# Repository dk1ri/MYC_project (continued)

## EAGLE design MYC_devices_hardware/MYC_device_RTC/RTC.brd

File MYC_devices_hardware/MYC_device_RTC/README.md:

#Real Time Clock
This is a device, which can deliver 
accurate time data to a MYC system

The DCF RTC board by ELV is used, which receives the DCF77 signal from Franfurt.

For details of the MYC protocol see the documentation or read www.dk1ri.de -> MYC

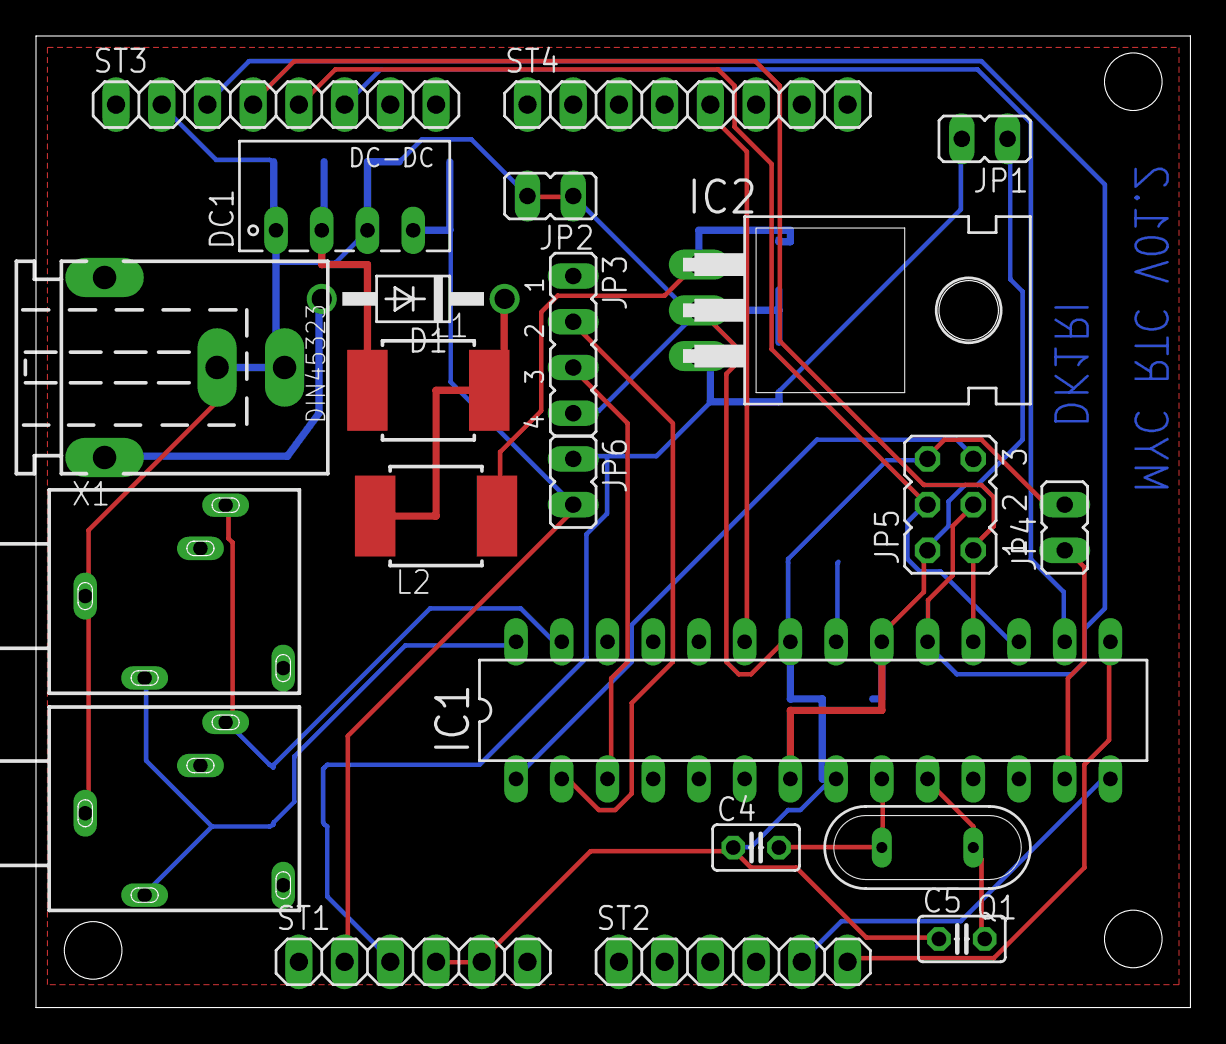
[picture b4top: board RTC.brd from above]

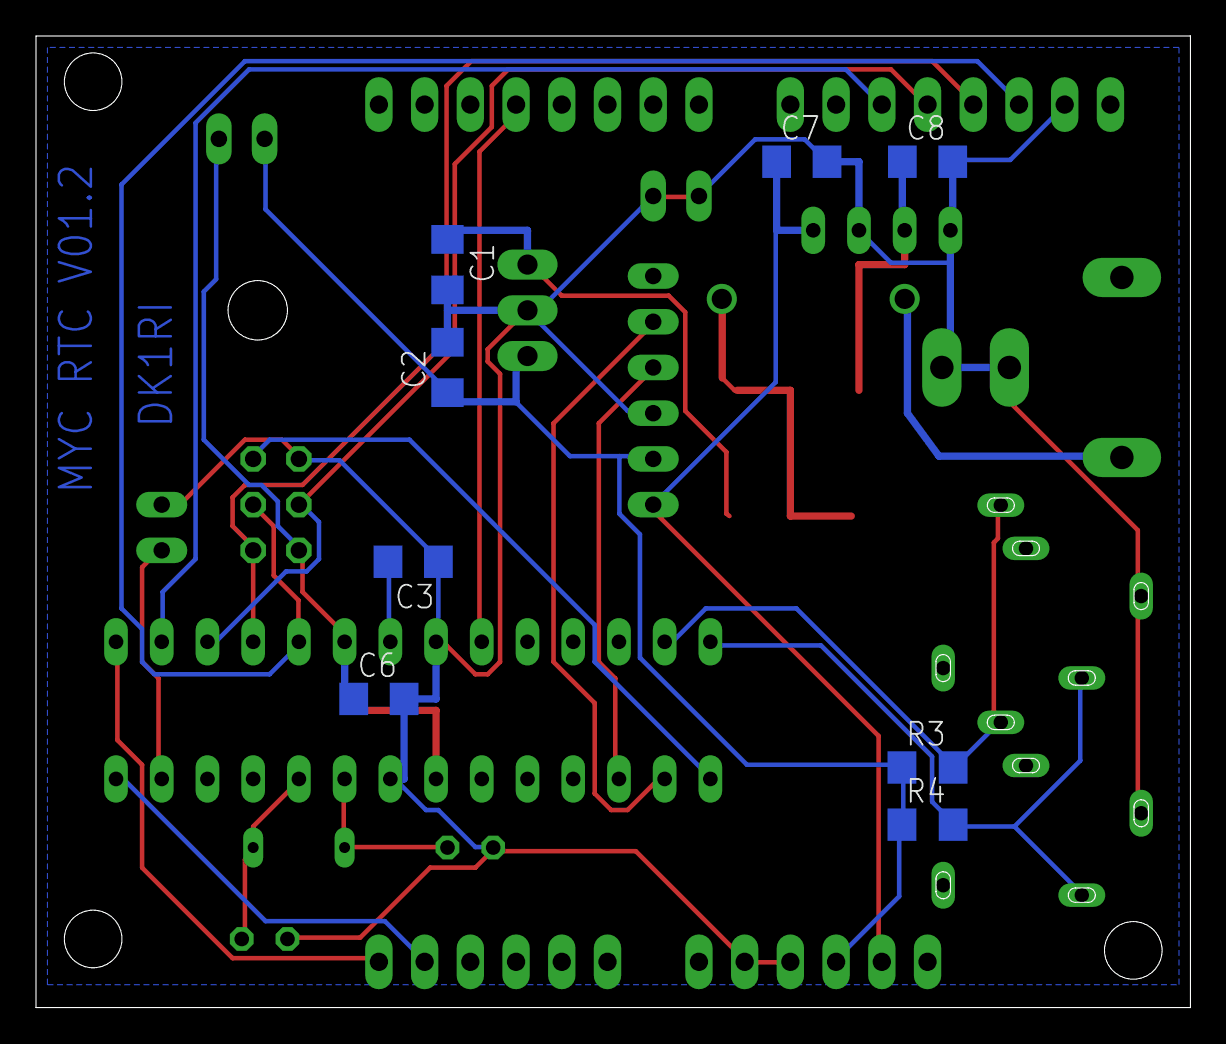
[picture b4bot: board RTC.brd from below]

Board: 2 copper layers, 64.1 x 54.0 mm, 30 parts (8 on the bottom side), 24 nets.

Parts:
C1, C2, C3, C6, C7, C8: 22uF 1210; C1206
C4, C5: 18pF; C025-025X050
D1: 1N4004; DO41-10
DC1: AM1S1203SZ; NME
IC1: MEGA8-P; DIL28-3
IC2: 7805T; TO220H
JP1: Power; JP1
JP2: GND; JP1
JP3: USB; JP4
JP4: Reset; JP1
JP5: ISP; JP3Q
JP6: USB2; JP1
L1, L2: 100u; MS85
Q1: 20MHz; QS
R3, R4: 4k7; R1206
ST1: Power; 1X06
ST2: I2C; 1X06
ST3: SPI; 1X08
ST4: UART; 1X08
X1: 8-15V; 737992-5
X2, X3: 1503_09

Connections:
GND: C1.2, C2.2, C3.1, C4.1, C5.1, C6.2, C7.2, C8.2, DC1.1, DC1.3, IC1.8, IC1.22, IC2.2, JP2.1, JP2.2, JP3.4, JP4.2, JP5.6, ST1.4, ST1.5, ST3.2, X1.+, X1.K, X2.1, X3.1
unnamed: IC1.23, ST4.5
unnamed: IC1.14, ST2.5
unnamed: C8.1, DC1.2, L1.2
unnamed: IC1.16, ST3.6
unnamed: IC1.27, R3.2, X2.3, X3.3
unnamed: IC1.13, JP4.1
unnamed: D1.C, L1.1, L2.1
unnamed: IC1.3, JP3.3
unnamed: IC1.2, JP3.2
unnamed: IC1.15, ST2.6
unnamed: IC1.18, JP5.1, ST3.4
unnamed: IC1.1, JP5.5
unnamed: C4.2, IC1.9, Q1.2
unnamed: IC1.19, JP5.3, ST3.3
unnamed: IC1.28, R4.2, X2.2, X3.2
unnamed: D1.A, X1.-1
unnamed: IC1.17, JP5.4, ST3.5
unnamed: C1.1, IC2.1, L2.2
unnamed: C3.2, IC1.21
unnamed: C5.2, IC1.10, Q1.1
unnamed: C6.1, IC1.7, IC1.20, JP1.1, JP5.2
VDD: C2.1, IC2.3, JP1.2, JP6.1, R3.1, R4.1, ST1.3
VSS: C7.1, DC1.4, JP6.2, ST1.2

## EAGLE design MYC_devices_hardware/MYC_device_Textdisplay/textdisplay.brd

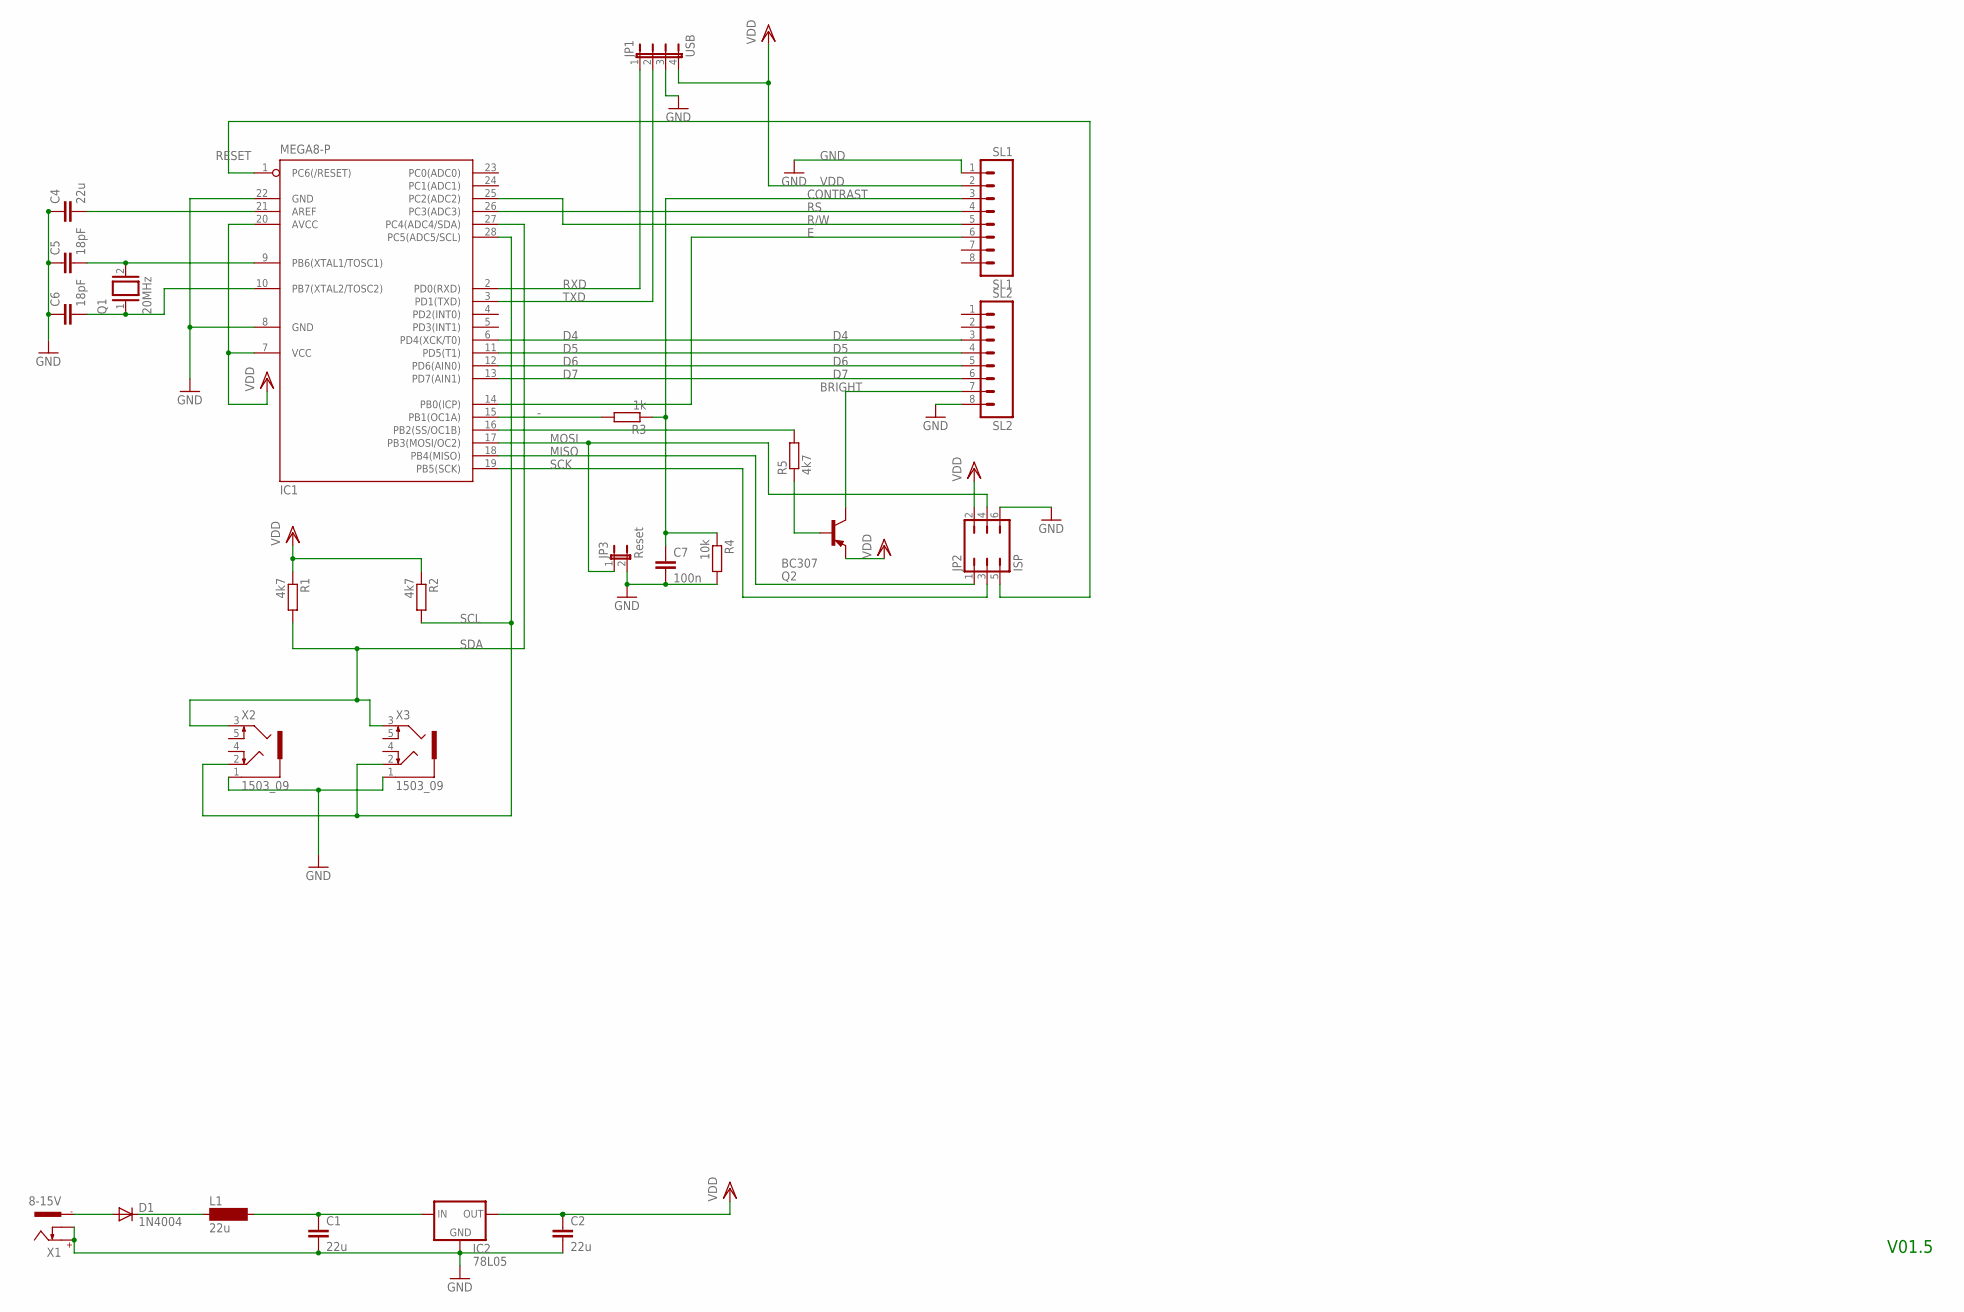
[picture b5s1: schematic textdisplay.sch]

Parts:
C1, C2, C4: 22u; C1206
C5, C6: 18pF; C025-025X050
C7: 100n; C050-025X075
D1: 1N4004; DO41-10
IC1: MEGA8-P; DIL28-3
IC2: 78L05; 78LXX
JP1: USB; JP4
JP2: ISP; JP3Q
JP3: Reset; JP1
L1: 22u; MS85
Q1: 20MHz; QS
Q2: BC307; TO92
R1, R2, R5: 4k7; 0207/2V
R3: 1k; 0207/2V
R4: 10k; 0207/2V
SL1: SL1; 08P
SL2: SL2; 08P
X1: 8-15V; 737992-5
X2, X3: 1503_09

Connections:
-: IC1.15 (PB1(OC1A)), R3.2
BRIGHT: Q2.3 (C), SL2.7
CONTRAST: C7.1, R3.1, R4.1, SL1.3
D4: IC1.6 (PD4(XCK/T0)), SL2.3
D5: IC1.11 (PD5(T1)), SL2.4
D6: IC1.12 (PD6(AIN0)), SL2.5
D7: IC1.13 (PD7(AIN1)), SL2.6
E: IC1.14 (PB0(ICP)), SL1.6
GND: C1.2, C2.2, C4.1, C5.1, C6.1, C7.2, IC1.8 (GND), IC1.22 (GND), IC2.GND, JP1.3, JP2.6, JP3.2, R4.2, SL1.1, SL2.8, X1.+, X1.K, X2.1, X3.1
MISO: IC1.18 (PB4(MISO)), JP2.1
MOSI: IC1.17 (PB3(MOSI/OC2)), JP2.4, JP3.1
unnamed: D1.C, L1.1
unnamed: IC1.16 (PB2(SS/OC1B)), R5.2
unnamed: Q2.2 (B), R5.1
unnamed: C1.1, IC2.IN, L1.2
unnamed: C5.2, IC1.9 (PB6(XTAL1/TOSC1)), Q1.2
unnamed: D1.A, X1.-1
unnamed: C4.2, IC1.21 (AREF)
unnamed: C6.2, IC1.10 (PB7(XTAL2/TOSC2)), Q1.1
R/W: IC1.25 (PC2(ADC2)), SL1.5
RESET: IC1.1 (PC6(/RESET)), JP2.5
RS: IC1.26 (PC3(ADC3)), SL1.4
RXD: IC1.2 (PD0(RXD)), JP1.1
SCK: IC1.19 (PB5(SCK)), JP2.3
SCL: IC1.28 (PC5(ADC5/SCL)), R2.2, X2.2, X3.2
SDA: IC1.27 (PC4(ADC4/SDA)), R1.2, X2.3, X3.3
TXD: IC1.3 (PD1(TXD)), JP1.2
VDD: C2.1, IC1.7 (VCC), IC1.20 (AVCC), IC2.OUT, JP1.4, JP2.2, Q2.1 (E), R1.1, R2.1, SL1.2

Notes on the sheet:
V01.5

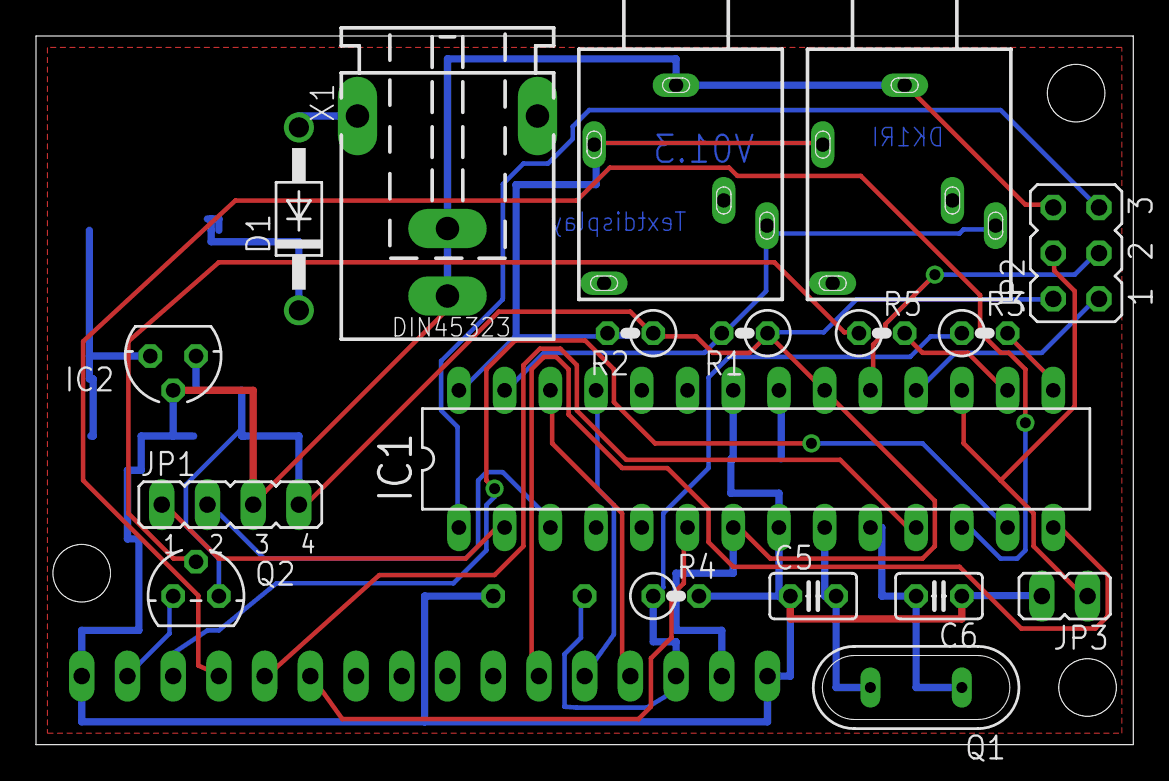
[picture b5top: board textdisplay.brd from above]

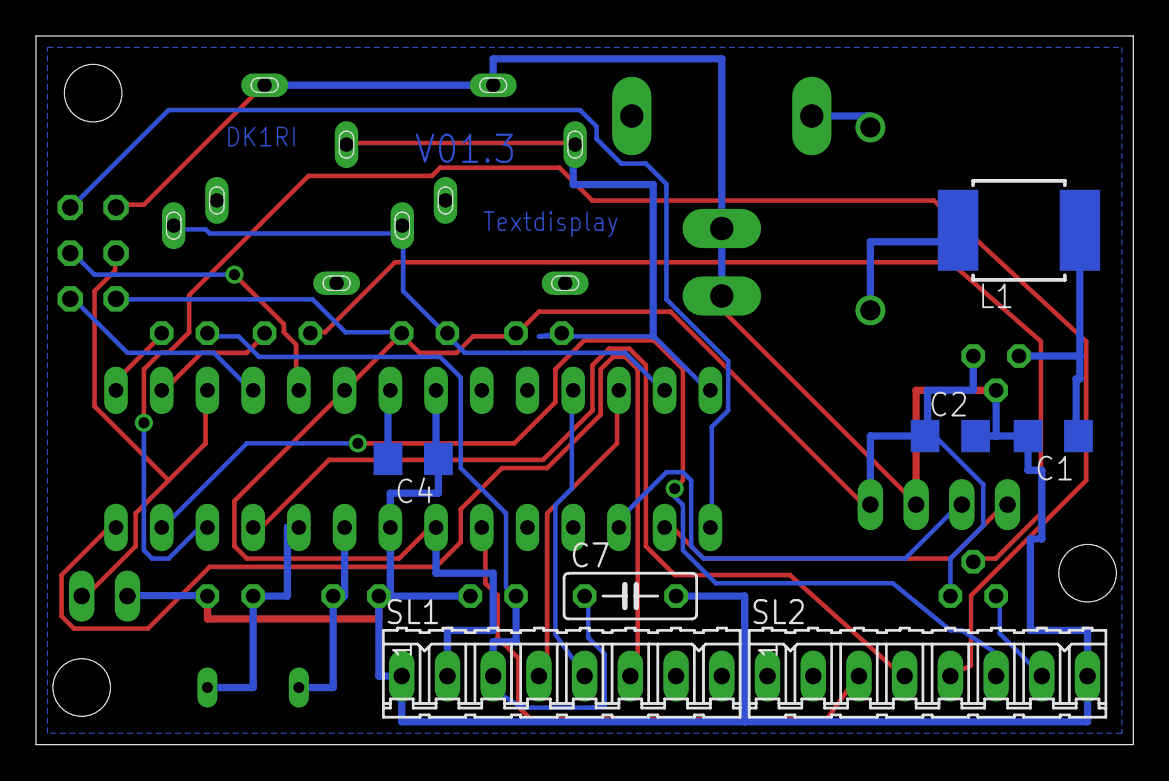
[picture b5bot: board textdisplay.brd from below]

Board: 2 copper layers, 61.0 x 39.4 mm, 25 parts (7 on the bottom side), 28 nets.

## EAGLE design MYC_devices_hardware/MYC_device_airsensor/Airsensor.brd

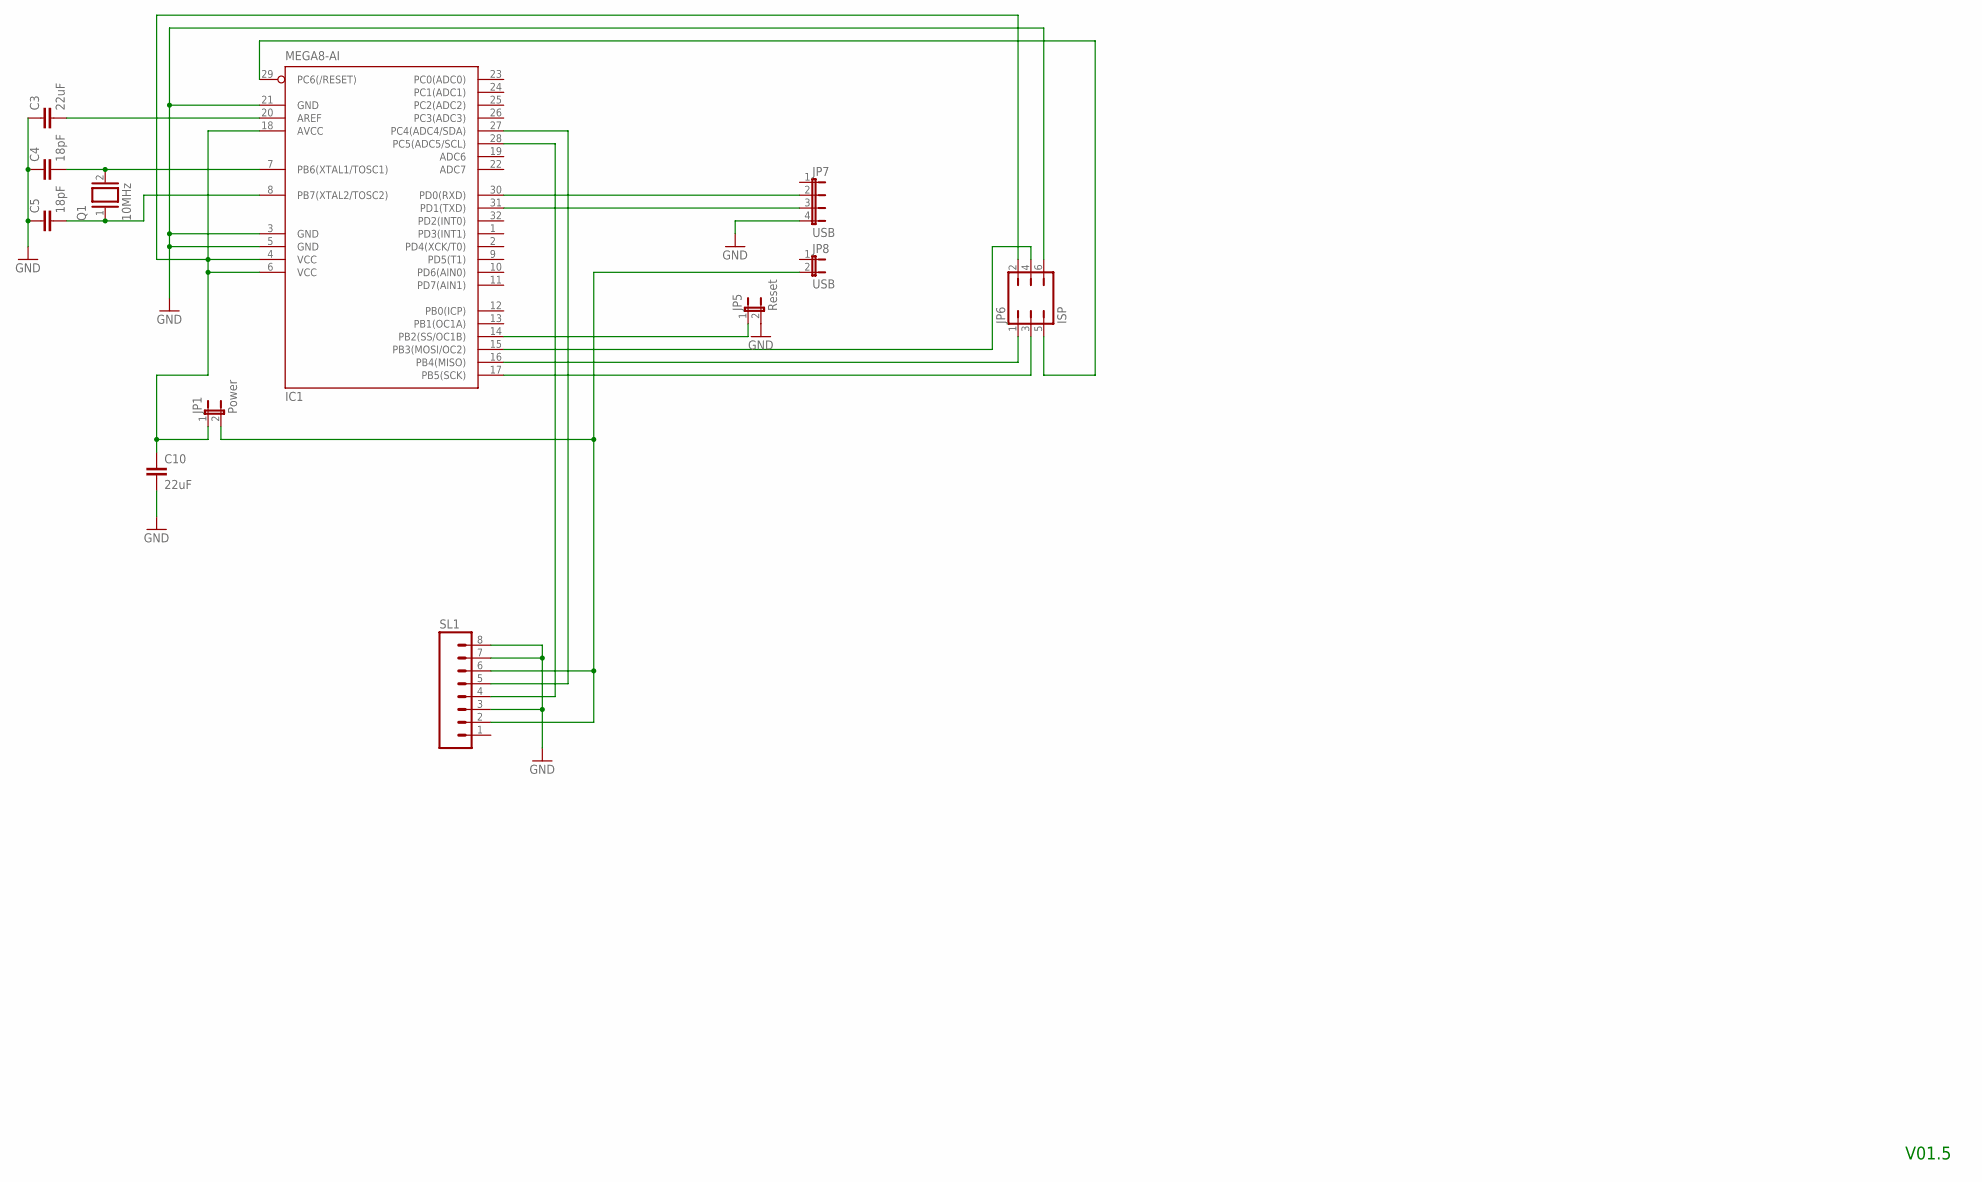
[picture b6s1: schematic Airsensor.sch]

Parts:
C3, C10: 22uF; C1206
C4, C5: 18pF; C025-025X050
IC1: MEGA8-AI; TQFP32-08
JP1: Power; JP1
JP5: Reset; JP1
JP6: ISP; JP3Q
JP7: USB; JP4
JP8: USB; JP1
Q1: 10MHz; QS
SL1: M08; 08P

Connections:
GND: C3.1, C4.1, C5.1, C10.2, IC1.3 (GND), IC1.5 (GND), IC1.21 (GND), JP5.2, JP6.6, JP7.4, SL1.3, SL1.7, SL1.8
unnamed: IC1.28 (PC5(ADC5/SCL)), SL1.4
unnamed: IC1.15 (PB3(MOSI/OC2)), JP6.4
unnamed: JP1.2, JP8.2, SL1.2, SL1.6
unnamed: IC1.17 (PB5(SCK)), JP6.3
unnamed: IC1.31 (PD1(TXD)), JP7.3
unnamed: IC1.14 (PB2(SS/OC1B)), JP5.1
unnamed: IC1.27 (PC4(ADC4/SDA)), SL1.5
unnamed: C3.2, IC1.20 (AREF)
unnamed: IC1.16 (PB4(MISO)), JP6.1
unnamed: IC1.29 (PC6(/RESET)), JP6.5
unnamed: C4.2, IC1.7 (PB6(XTAL1/TOSC1)), Q1.2
unnamed: C10.1, IC1.4 (VCC), IC1.6 (VCC), IC1.18 (AVCC), JP1.1, JP6.2
unnamed: IC1.30 (PD0(RXD)), JP7.2
unnamed: C5.2, IC1.8 (PB7(XTAL2/TOSC2)), Q1.1

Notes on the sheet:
V01.5

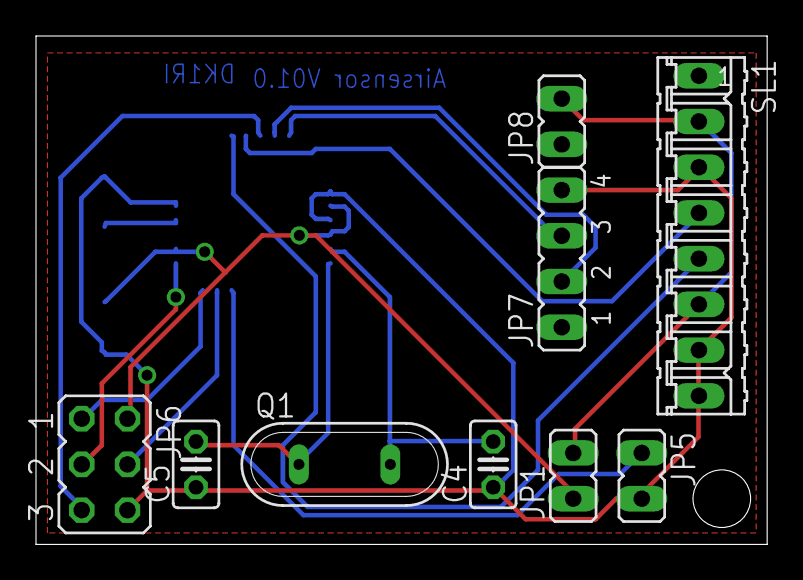
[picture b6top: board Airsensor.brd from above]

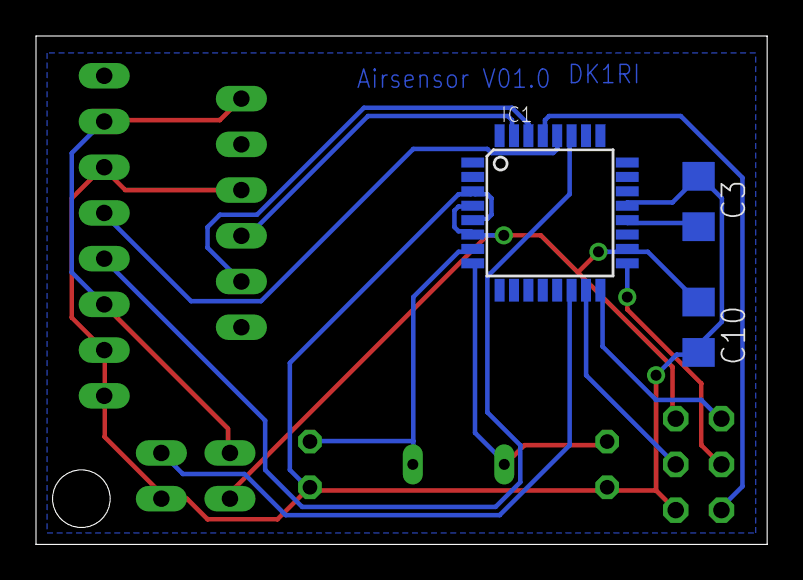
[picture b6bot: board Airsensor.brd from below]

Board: 2 copper layers, 40.6 x 28.2 mm, 12 parts (3 on the bottom side), 15 nets.

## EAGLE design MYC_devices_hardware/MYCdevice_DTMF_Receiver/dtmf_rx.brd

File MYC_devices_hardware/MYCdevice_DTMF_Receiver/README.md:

#DTMF Receiver
This is a MYC device, which can read DTMF Codes

The board can be also used standalone.

For details of the MYC protocol see the documentation or read www.dk1ri.de -> MYC

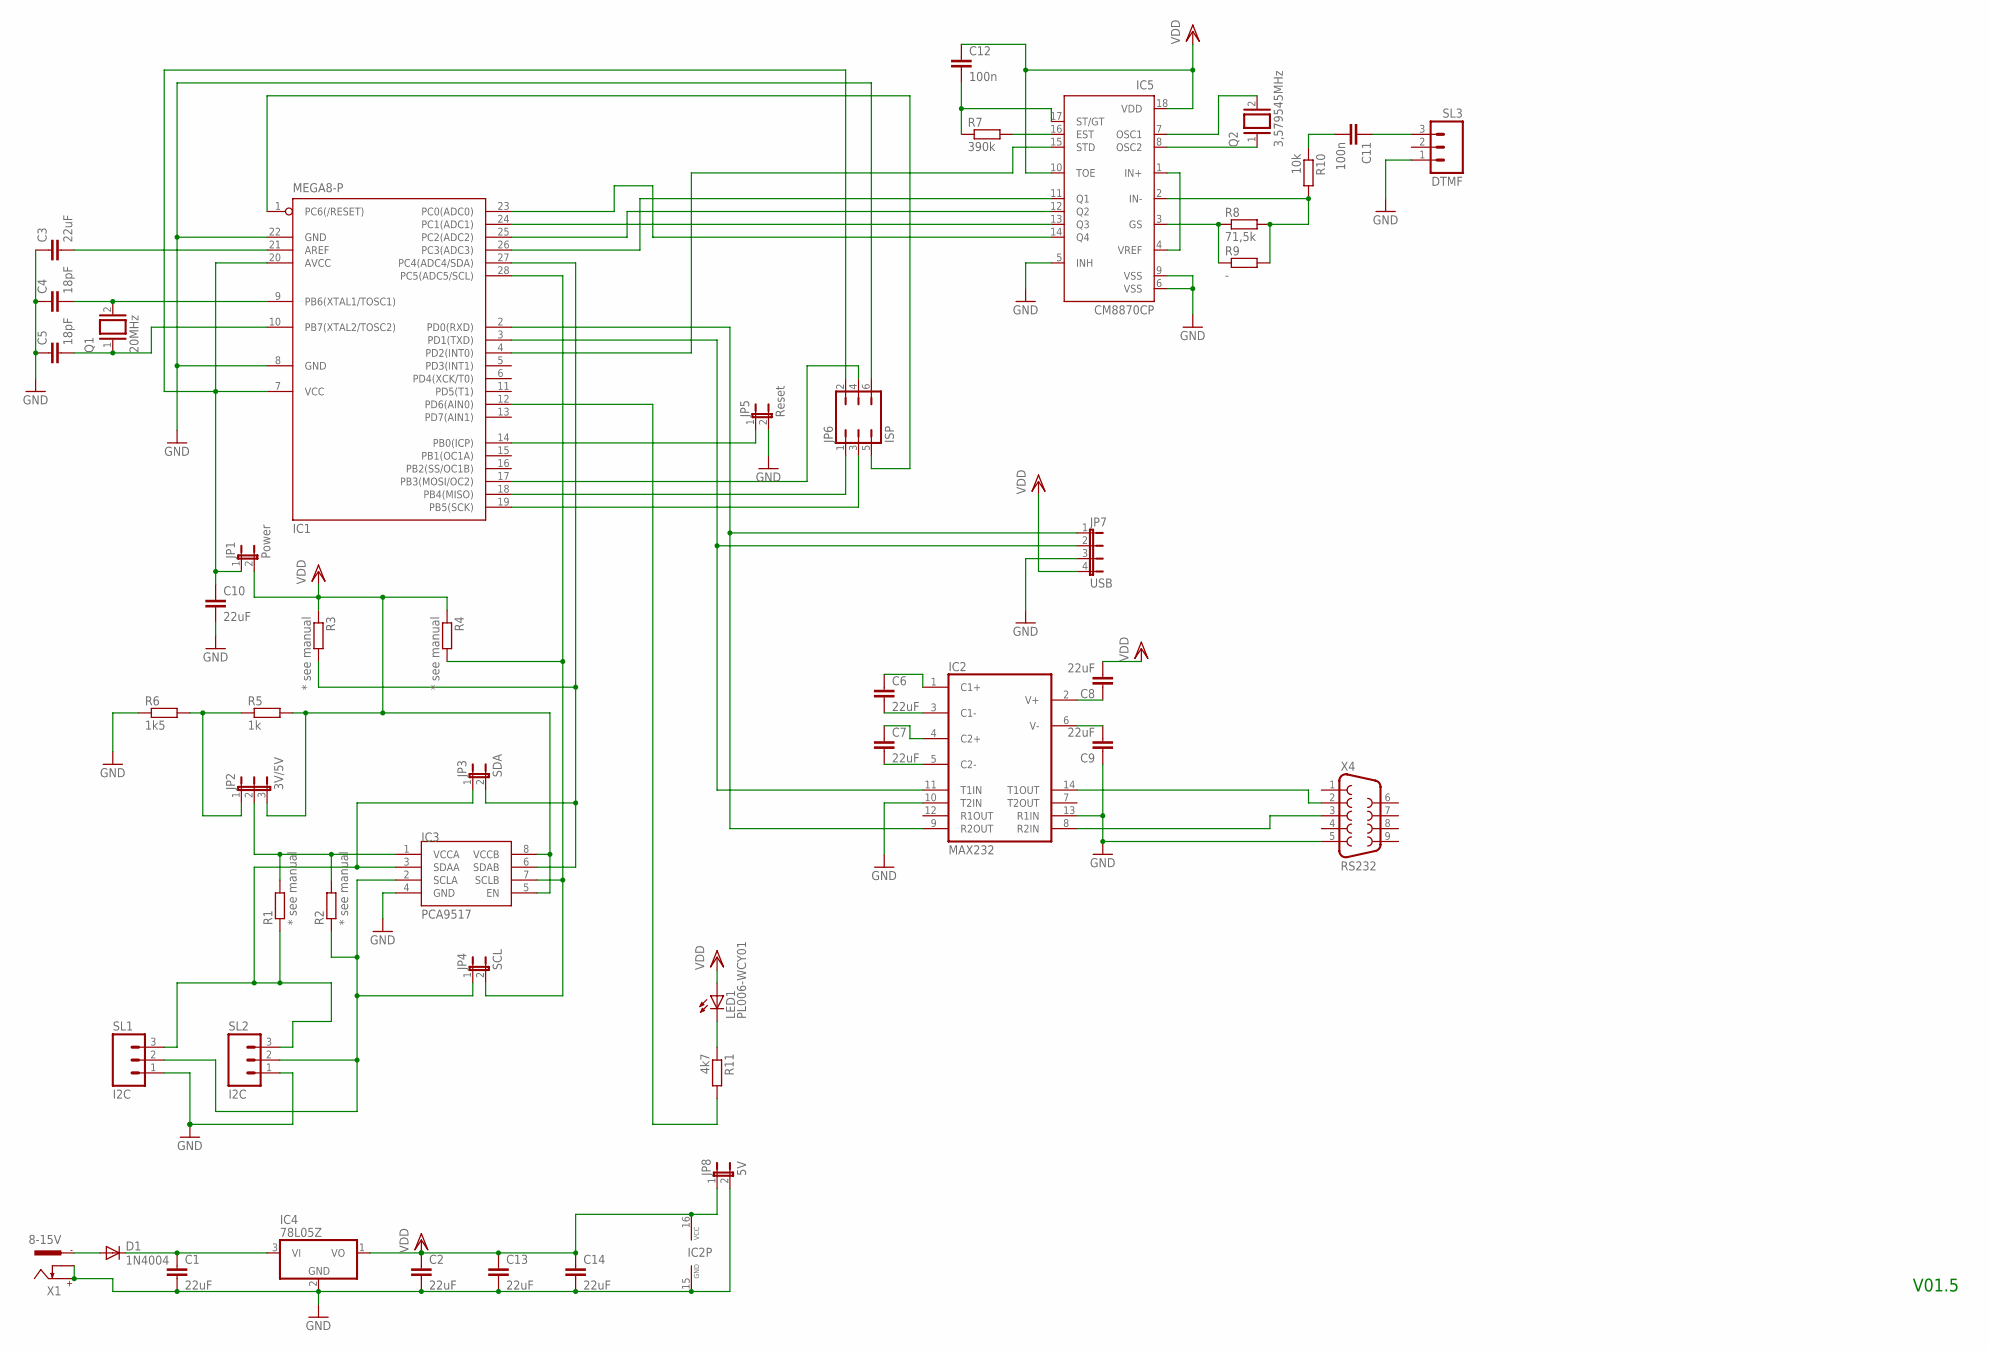
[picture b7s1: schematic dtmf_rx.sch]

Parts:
C1, C2, C3, C6, C7, C8, C9, C10, C13, C14: 22uF; C1206
C4, C5: 18pF; C025-025X050
C11, C12: 100n; C050-025X075
D1: 1N4004; DO41-10
IC1: MEGA8-P; DIL28-3
IC2: MAX232; DIL16
IC3: PCA9517; SO-08
IC4: 78L05Z; TO92
IC5: CM8870CP; DIL18
JP1: Power; JP1
JP2: 3V/5V; JP2
JP3: SDA; JP1
JP4: SCL; JP1
JP5: Reset; JP1
JP6: ISP; JP3Q
JP7: USB; JP4
JP8: 5V; JP1
LED1: PL006-WCY01; SOT23
Q1: 20MHz; QS
Q2: 3,579545MHz; QS
R1, R2, R3, R4: * see manual; R1206
R5: 1k; R1206
R6: 1k5; R1206
R7: 390k; R1206
R8: 71,5k; R1206
R9: -; R1206
R10: 10k; R1206
R11: 4k7; R1206
SL1, SL2: I2C; 03P
SL3: DTMF; 03P
X1: 8-15V; 737992-5
X4: RS232; F09H

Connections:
C13: C6.1, IC2.1 (C1+)
GND: C1.2, C2.2, C3.1, C4.1, C5.1, C9.1, C10.2, C13.2, C14.2, IC1.8 (GND), IC1.22 (GND), IC2.10 (T2IN), IC2.13 (R1IN), IC2.15 (GND), IC3.4 (GND), IC4.2 (GND), IC5.5 (INH), IC5.6 (VSS), IC5.9 (VSS), JP5.2, JP6.6, JP7.3, JP8.2, R6.1, SL1.1, SL2.1, SL3.1, X1.+, X1.K, X4.5
unnamed: IC1.12 (PD6(AIN0)), R11.2
unnamed: IC1.2 (PD0(RXD)), IC2.9 (R2OUT), JP7.1
unnamed: C7.2, IC2.5 (C2-)
unnamed: IC2.14 (T1OUT), X4.2
unnamed: IC3.3 (SDAA), JP3.1, R1.1, SL1.3, SL2.3
unnamed: IC1.14 (PB0(ICP)), JP5.1
unnamed: IC5.1 (IN+), IC5.4 (VREF)
unnamed: IC1.23 (PC0(ADC0)), IC5.14 (Q4)
unnamed: JP2.1, R5.1, R6.2
unnamed: IC2.8 (R2IN), X4.3
unnamed: IC1.3 (PD1(TXD)), IC2.11 (T1IN), JP7.2
unnamed: C7.1, IC2.4 (C2+)
unnamed: C6.2, IC2.3 (C1-)
unnamed: IC1.18 (PB4(MISO)), JP6.1
unnamed: C8.1, IC2.2 (V+)
unnamed: C9.2, IC2.6 (V-)
unnamed: IC1.1 (PC6(/RESET)), JP6.5
unnamed: C4.2, IC1.9 (PB6(XTAL1/TOSC1)), Q1.2
unnamed: IC1.19 (PB5(SCK)), JP6.3
unnamed: C11.1, SL3.3
unnamed: IC1.28 (PC5(ADC5/SCL)), IC3.7 (SCLB), JP4.2, R4.2
unnamed: C11.2, R10.1
unnamed: IC5.2 (IN-), R8.2, R9.2, R10.2
unnamed: IC5.3 (GS), R8.1, R9.1
unnamed: D1.A, X1.-1
unnamed: IC1.17 (PB3(MOSI/OC2)), JP6.4
unnamed: IC5.8 (OSC2), Q2.1
unnamed: IC1.24 (PC1(ADC1)), IC5.13 (Q3)
unnamed: IC5.7 (OSC1), Q2.2
unnamed: IC5.16 (EST), R7.2
unnamed: C1.1, D1.C, IC4.3 (VI)
unnamed: IC1.26 (PC3(ADC3)), IC5.11 (Q1)
unnamed: C3.2, IC1.21 (AREF)
unnamed: IC1.27 (PC4(ADC4/SDA)), IC3.6 (SDAB), JP3.2, R3.2
unnamed: C5.2, IC1.10 (PB7(XTAL2/TOSC2)), Q1.1
unnamed: IC1.25 (PC2(ADC2)), IC5.12 (Q2)
unnamed: IC3.2 (SCLA), JP4.1, R2.1, SL1.2, SL2.2
unnamed: C12.2, IC5.17 (ST/GT), R7.1
unnamed: IC1.4 (PD2(INT0)), IC5.15 (STD)
unnamed: IC3.1 (VCCA), JP2.2, R1.2, R2.2
unnamed: C10.1, IC1.7 (VCC), IC1.20 (AVCC), JP1.1, JP6.2
unnamed: LED1.3 (C), R11.1
VDD: C2.1, C8.2, C12.1, C13.1, C14.1, IC2.16 (VCC), IC3.5 (EN), IC3.8 (VCCB), IC4.1 (VO), IC5.10 (TOE), IC5.18 (VDD), JP1.2, JP2.3, JP7.4, JP8.1, LED1.1 (A), R3.1, R4.1, R5.2

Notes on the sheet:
V01.5

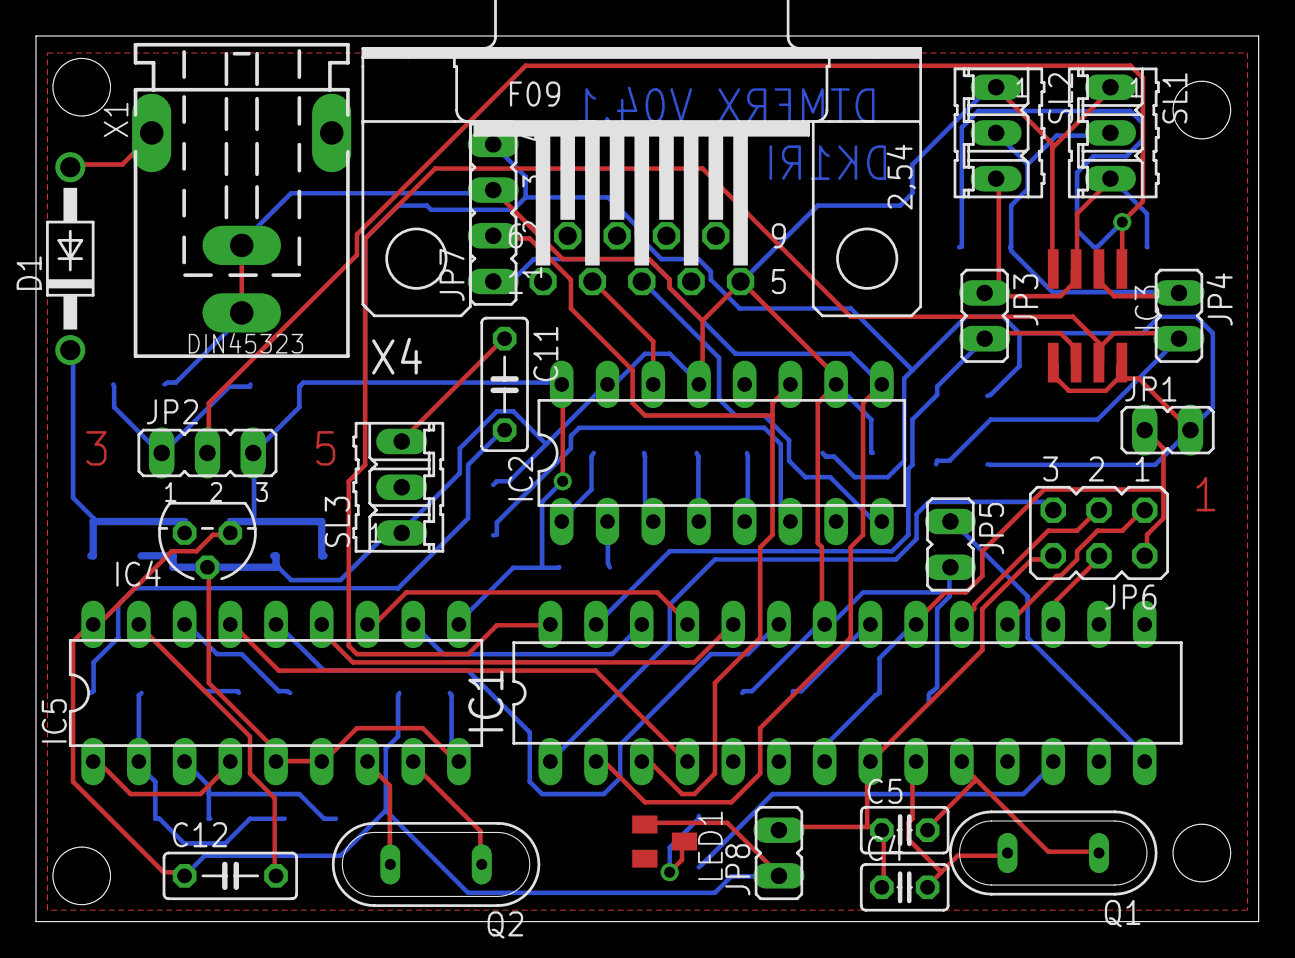
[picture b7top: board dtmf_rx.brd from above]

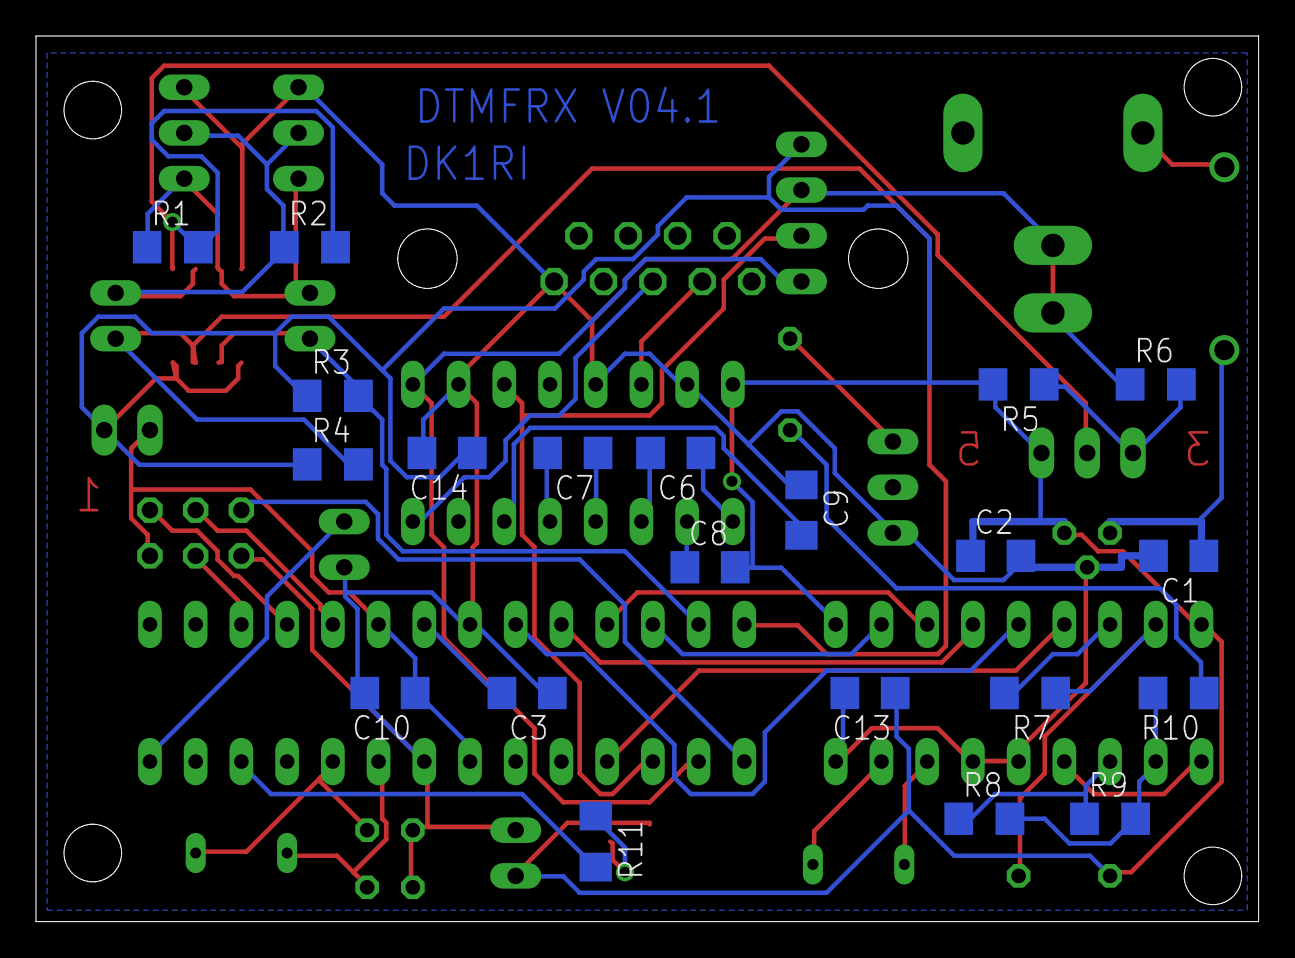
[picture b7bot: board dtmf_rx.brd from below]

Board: 2 copper layers, 67.9 x 49.2 mm, 47 parts (21 on the bottom side), 45 nets.
